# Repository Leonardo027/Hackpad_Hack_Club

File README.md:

# [Macro Pad 4x4]
Hello! This is my submission for hackpad! This was made for Hackpad v1.

## Features
- 16x Mechanical MX Switches (4x4 Matrix)
- A smooth EC11 Rotary Encoder for volume/scrolling
- A crisp 0.91" OLED screen (128x32) for info and cat gifs
- Underglow RGB lighting (SK6812 MINI-E)
- Powered by Seeed XIAO RP2040
- KMK firmware! Fully programmable layers

## PCB
Here are pictures of my pcb design:

| **Schematic** | **PCB** |
|---------------|---------|
|||

I designed this to be compact but functional. The routing was a challenge but I learned a lot about KiCad!

[x] I ran DRC and there are 0 errors

## CAD
Designed using Autodesk Fusion 360!

It was a learning curve moving to 3D modeling, but I managed to create a case that snaps together (or uses screws). The OLED and Encoder fit perfectly in the top plate.

Everything fits together with standard M3 screws.

## Firmware

I wrote the firmware using KMK, you can see it inside the `Firmware` folder in this repo. It handles the matrix scanning, the encoder logic, and the OLED display.

## Notes
Making this pad was an amazing journey. I started not knowing much about Fusion 360 or advanced PCB routing, but with some help, I got to this final version. I was worried about the OLED placement, but the measurements turned out correct!

## BOM
- 1x Seeed XIAO RP2040
- 16x MX Style Switches
- 16x 1N4148 Diodes
- 1x EC11 Rotary Encoder + Knob
- 1x SSD1306 0.91" OLED Display (I2C)
- 16x SK6812 MINI-E LEDs (for underglow)
- 3D Printed Case (PLA/PETG)
- M3 Screws and Nuts

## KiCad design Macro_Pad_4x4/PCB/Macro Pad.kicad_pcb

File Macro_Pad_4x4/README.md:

# [Macro Pad 4x4]
Hello! This is my submission for hackpad! This was made for Hackpad v1.

## Features
- 16x Mechanical MX Switches (4x4 Matrix)
- A smooth EC11 Rotary Encoder for volume/scrolling
- A crisp 0.91" OLED screen (128x32) for info and cat gifs
- Underglow RGB lighting (SK6812 MINI-E)
- Powered by Seeed XIAO RP2040
- KMK firmware! Fully programmable layers

## PCB
Here are pictures of my pcb design:

| **Schematic** | **PCB** |
|---------------|---------|
|||

I designed this to be compact but functional. The routing was a challenge but I learned a lot about KiCad!

[x] I ran DRC and there are 0 errors

## CAD
Designed using Autodesk Fusion 360!

It was a learning curve moving to 3D modeling, but I managed to create a case that snaps together (or uses screws). The OLED and Encoder fit perfectly in the top plate.

Everything fits together with standard M3 screws.

## Firmware

I wrote the firmware using KMK, you can see it inside the `Firmware` folder in this repo. It handles the matrix scanning, the encoder logic, and the OLED display.

## Notes
Making this pad was an amazing journey. I started not knowing much about Fusion 360 or advanced PCB routing, but with some help, I got to this final version. I was worried about the OLED placement, but the measurements turned out correct!

## BOM
- 1x Seeed XIAO RP2040
- 16x MX Style Switches
- 16x 1N4148 Diodes
- 1x EC11 Rotary Encoder + Knob
- 1x SSD1306 0.91" OLED Display (I2C)
- 16x SK6812 MINI-E LEDs (for underglow)
- 3D Printed Case (PLA/PETG)

- M3 Screws and Nuts

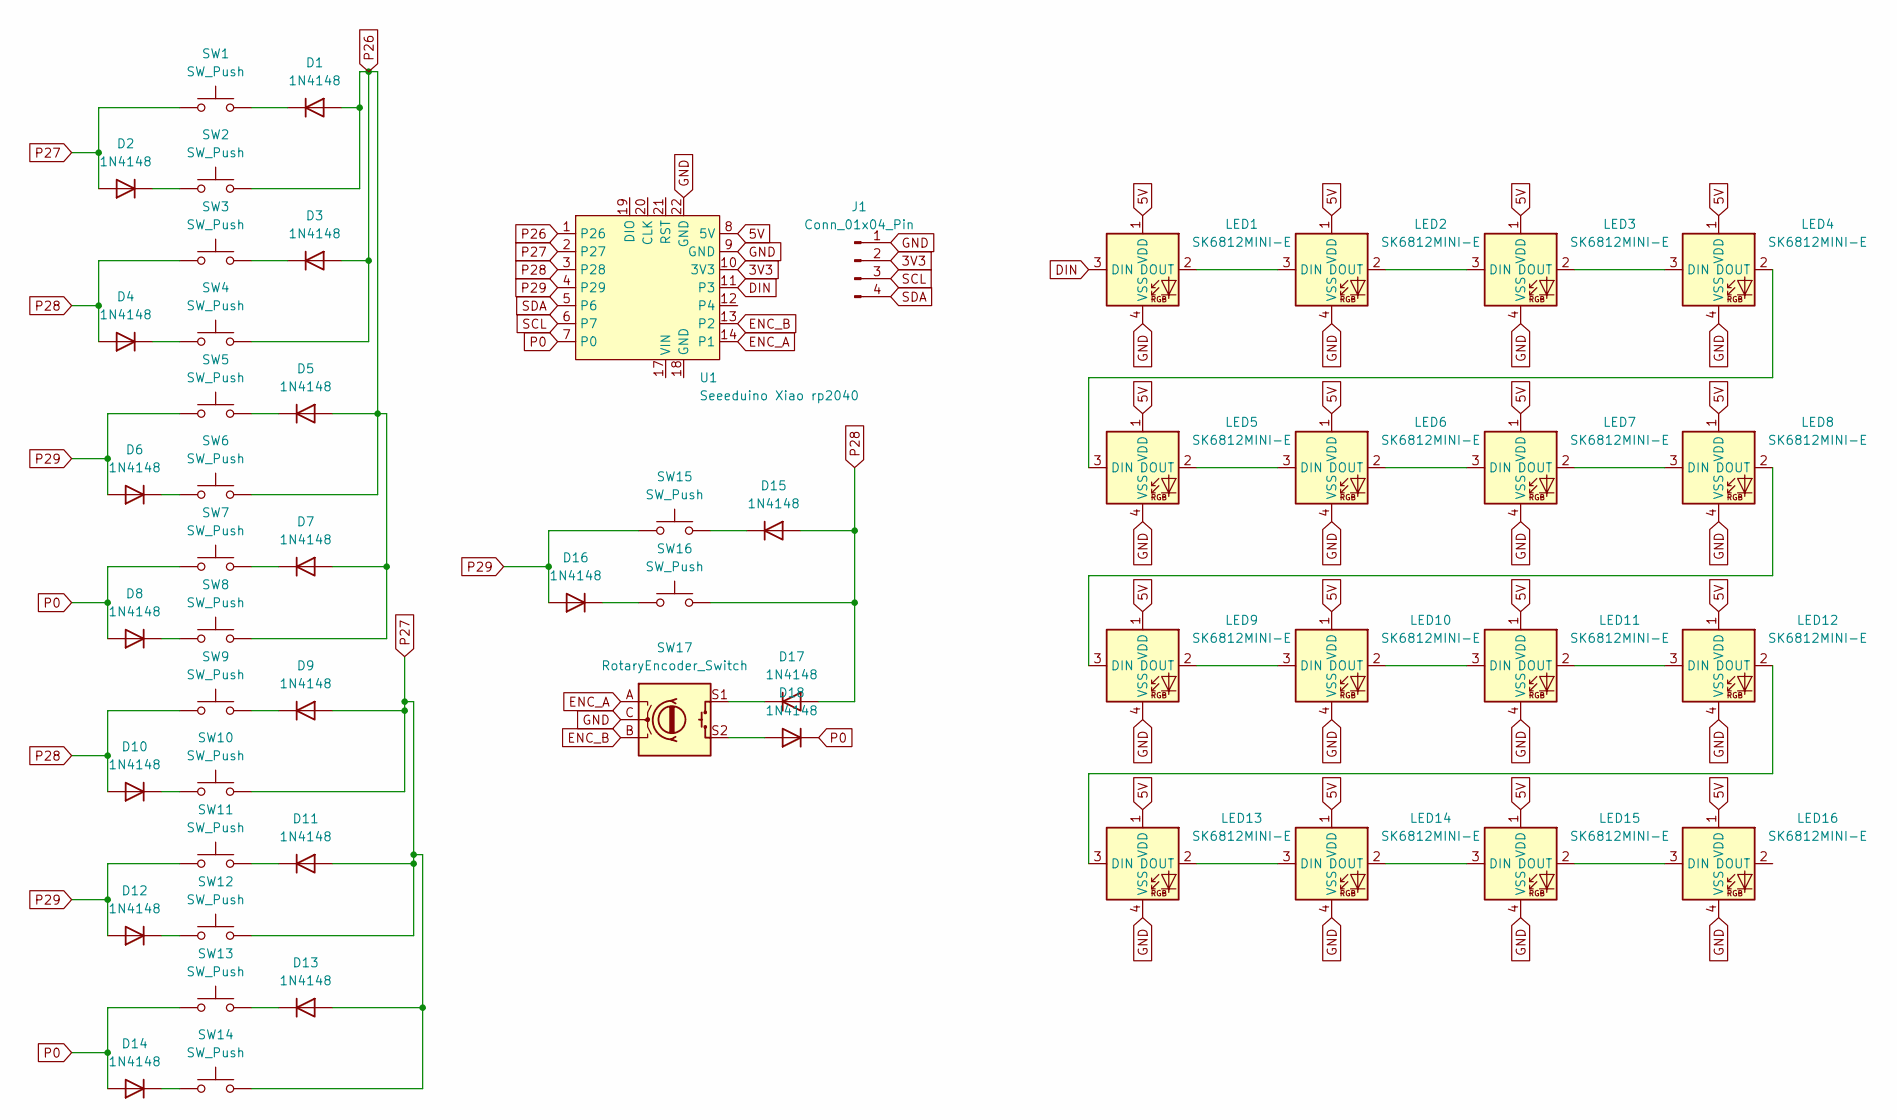
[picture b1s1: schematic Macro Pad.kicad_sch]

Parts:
D1, D2, D3, D4, D5, D6, D7, D8, D9, D10, D11, D12, D13, D14, D15, D16, D17, D18: 1N4148; D_DO-35_SOD27_P7.62mm_Horizontal
J1: Conn_01x04_Pin; PinHeader_1x04_P2.54mm_Vertical
LED1, LED2, LED3, LED4, LED5, LED6, LED7, LED8, LED9, LED10, LED11, LED12, LED13, LED14, LED15, LED16: SK6812MINI-E; LED_RGB_Wuerth-PLCC4_3.2x2.8mm_150141M173100
SW1, SW2, SW3, SW4, SW5, SW6, SW7, SW8, SW9, SW10, SW11, SW12, SW13, SW14, SW15, SW16: SW_Push; SW_Cherry_MX_1.00u_PCB
SW17: RotaryEncoder_Switch; RotaryEncoder_Alps_EC11E-Switch_Vertical_H20mm
U1: Seeeduino Xiao rp2040; Xiao_rp2040_ACH

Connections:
3V3: J1.2, U1.10 (3V3)
5V: LED1.1 (VDD), LED2.1 (VDD), LED3.1 (VDD), LED4.1 (VDD), LED5.1 (VDD), LED6.1 (VDD), LED7.1 (VDD), LED8.1 (VDD), LED9.1 (VDD), LED10.1 (VDD), LED11.1 (VDD), LED12.1 (VDD), LED13.1 (VDD), LED14.1 (VDD), LED15.1 (VDD), LED16.1 (VDD), U1.8 (5V)
DIN: LED1.3 (DIN), U1.11 (P3)
ENC_A: SW17.A, U1.14 (P1)
ENC_B: SW17.B, U1.13 (P2)
GND: J1.1, LED1.4 (VSS), LED2.4 (VSS), LED3.4 (VSS), LED4.4 (VSS), LED5.4 (VSS), LED6.4 (VSS), LED7.4 (VSS), LED8.4 (VSS), LED9.4 (VSS), LED10.4 (VSS), LED11.4 (VSS), LED12.4 (VSS), LED13.4 (VSS), LED14.4 (VSS), LED15.4 (VSS), LED16.4 (VSS), SW17.C, U1.9 (GND), U1.22 (GND)
unnamed: D1.1 (K), SW1.2
unnamed: D2.1 (K), SW2.1
unnamed: D3.1 (K), SW3.2
unnamed: D4.1 (K), SW4.1
unnamed: D5.1 (K), SW5.2
unnamed: D6.1 (K), SW6.1
unnamed: D7.1 (K), SW7.2
unnamed: D8.1 (K), SW8.1
unnamed: D9.1 (K), SW9.2
unnamed: D10.1 (K), SW10.1
unnamed: D11.1 (K), SW11.2
unnamed: D12.1 (K), SW12.1
unnamed: D13.1 (K), SW13.2
unnamed: D14.1 (K), SW14.1
unnamed: D15.1 (K), SW15.2
unnamed: D16.1 (K), SW16.1
unnamed: D17.1 (K), SW17.S1
unnamed: D18.2 (A), SW17.S2
unnamed: LED1.2 (DOUT), LED2.3 (DIN)
unnamed: LED2.2 (DOUT), LED3.3 (DIN)
unnamed: LED3.2 (DOUT), LED4.3 (DIN)
unnamed: LED4.2 (DOUT), LED5.3 (DIN)
unnamed: LED5.2 (DOUT), LED6.3 (DIN)
unnamed: LED6.2 (DOUT), LED7.3 (DIN)
unnamed: LED7.2 (DOUT), LED8.3 (DIN)
unnamed: LED8.2 (DOUT), LED9.3 (DIN)
unnamed: LED9.2 (DOUT), LED10.3 (DIN)
unnamed: LED10.2 (DOUT), LED11.3 (DIN)
unnamed: LED11.2 (DOUT), LED12.3 (DIN)
unnamed: LED12.2 (DOUT), LED13.3 (DIN)
unnamed: LED13.2 (DOUT), LED14.3 (DIN)
unnamed: LED14.2 (DOUT), LED15.3 (DIN)
unnamed: LED15.2 (DOUT), LED16.3 (DIN)
P0: D8.2 (A), D14.2 (A), D18.1 (K), SW7.1, SW13.1, U1.7 (P0)
P26: D1.2 (A), D3.2 (A), D5.2 (A), D7.2 (A), SW2.2, SW4.2, SW6.2, SW8.2, U1.1 (P26)
P27: D2.2 (A), D9.2 (A), D11.2 (A), D13.2 (A), SW1.1, SW10.2, SW12.2, SW14.2, U1.2 (P27)
P28: D4.2 (A), D10.2 (A), D15.2 (A), D17.2 (A), SW3.1, SW9.1, SW16.2, U1.3 (P28)
P29: D6.2 (A), D12.2 (A), D16.2 (A), SW5.1, SW11.1, SW15.1, U1.4 (P29)
SCL: J1.3, U1.6 (P7)
SDA: J1.4, U1.5 (P6)

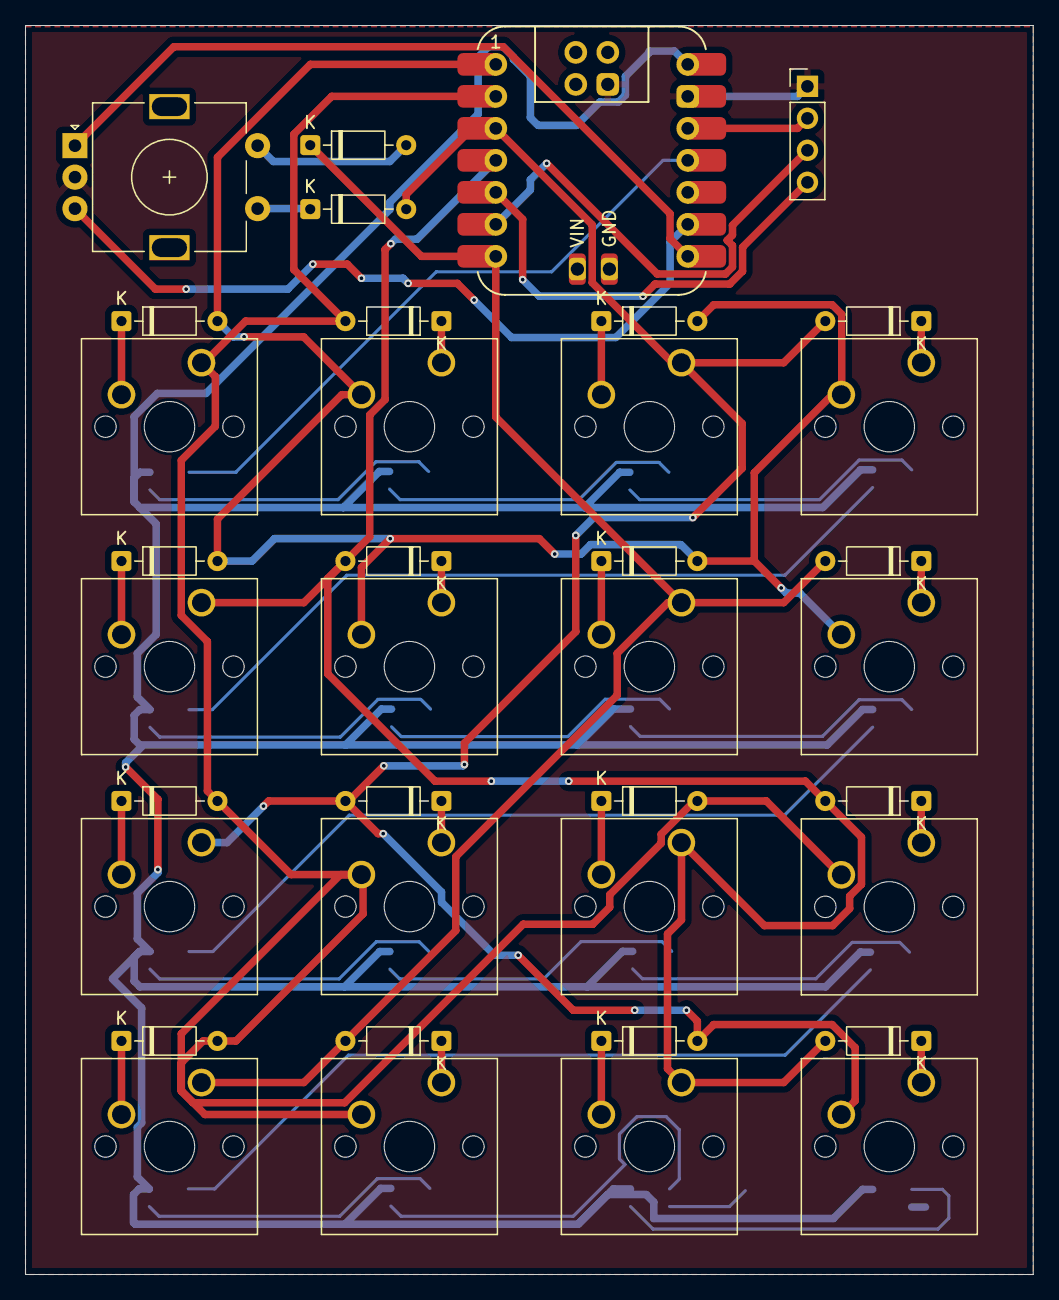
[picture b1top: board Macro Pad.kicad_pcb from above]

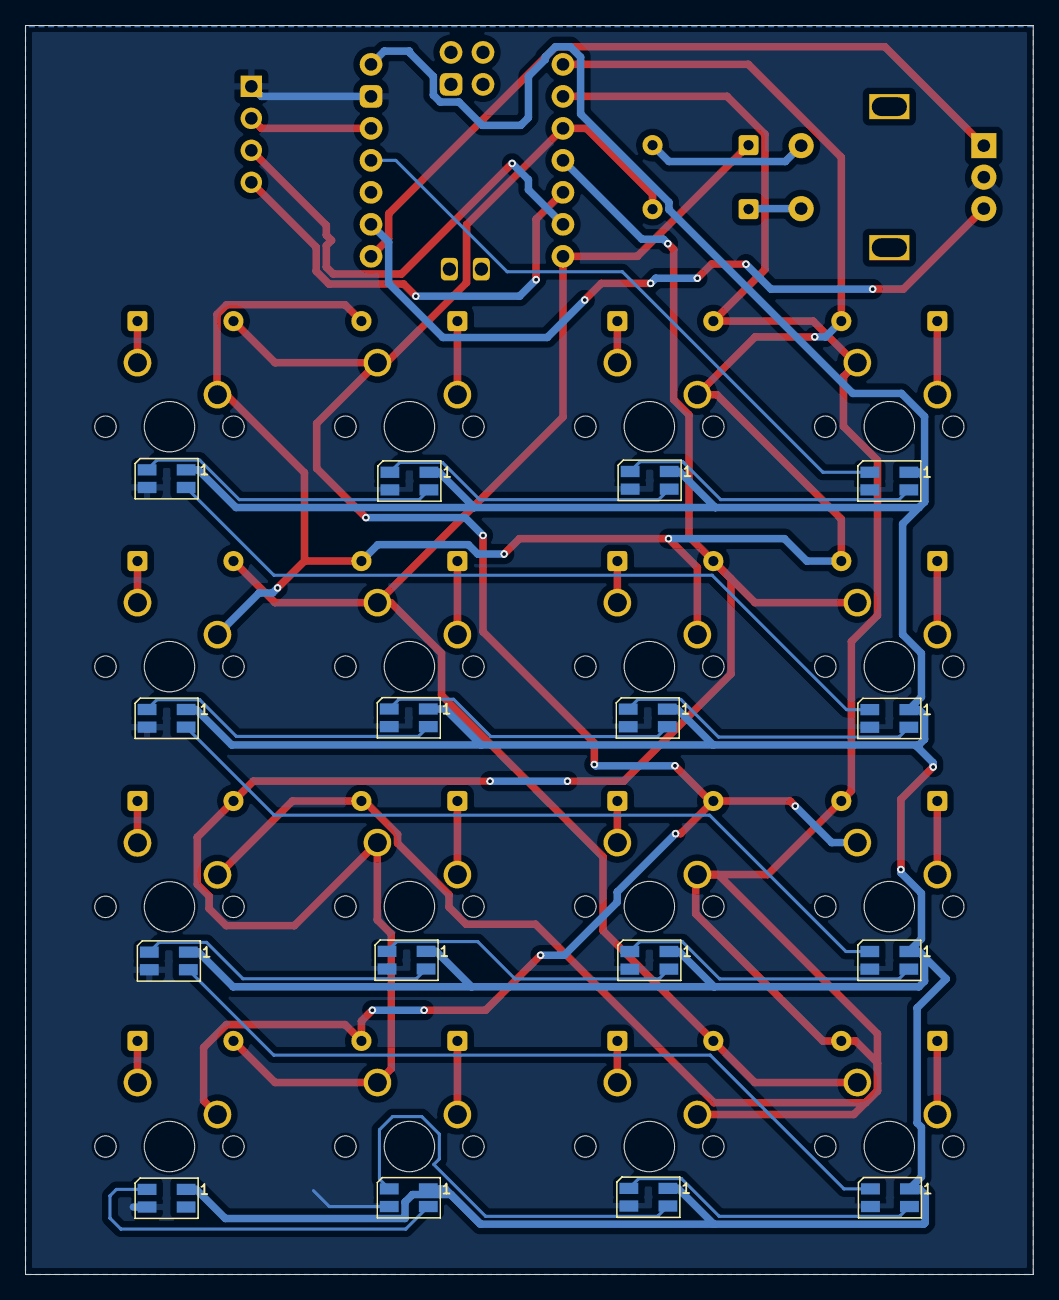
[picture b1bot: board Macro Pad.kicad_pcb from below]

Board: 2 copper layers, 80.0 x 99.2 mm, 53 parts (16 on the bottom side), 46 nets.

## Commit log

2026-01-08 Add project description to README
    Added project overview and technical details.
2026-01-08 Format README.md with proper Markdown syntax
2026-01-11 Add README for Macro Pad 4x4 project
    Added detailed information about the Macro Pad 4x4 project, including features, PCB design, CAD, firmware, notes, and BOM.
2026-01-11 Update README.md formatting and content
2026-01-11 Change image extensions to uppercase .PNG
    Updated image file extensions from .png to .PNG for consistency.
